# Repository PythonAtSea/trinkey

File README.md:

# Trinkey

Trinkey is a STM32 based keychain trinket. It has two Kailh switches, each with  a MBK low profile keycap and a reverse mounted SK6812MINI-E RGB LED. Additionally, there are two more reverse mounted SK6812MINI-E next to the keyring. It also has a male USB-A plug which powers the device and provides USB FS connectivity. 

## Screenshots

##### SVG export of schematic

##### Combined export of PCB

##### Top export of PCB

##### Bottom export of PCB

## Flashing Software

The Trinkey has pads for flashing using **S**erial **W**ire **D**ebug. If you're getting one of these thru [Hack Club Gadget Market](https://gadget.hackclub.com), it will be pre flashing with a bootloader that supports uploading code over USB using the Ardunio IDE. It will also have some sort of example program, but that is still TBD. I will also design a jig for holding contact against the test pads for flashing over SWD.

## Bill of Materials

| Item | Vendor | Price |
|------|--------|-------|
|PCB|JLCPCB|$70.43|
|[USB-A plug](https://www.digikey.com/en/products/detail/molex/0480370001/857603)|Digikey|$10.38|
|Shipping|Digikey|$4.99|
|Tariff|Digikey|$2.08|
|Sales tax|Digikey|$1.22|
|[SK6812MINI-E (25 pack)](https://keeb.io/products/sk-6812-mini-e-rgb-leds-12-pack)|Keebs.io|$5.99|
|[Kailh low profile switches](https://keeb.io/products/kailh-choc-low-profile-switches-v1)|Keebs.io|$7.20|
|[MBK PBT Blank keycaps](https://keeb.io/products/mbk-keycaps)|Keebs.io|$4.41|
|Shipping|Keebs.io|$7.90|
|[ST-LINK/V2 (mini)](https://www.waveshare.com/st-link-v2-mini-stm32.htm)|Waveshare|$8.99|
|Shipping|Waveshare|$10.00|
|**Total**| |**$133.59**|

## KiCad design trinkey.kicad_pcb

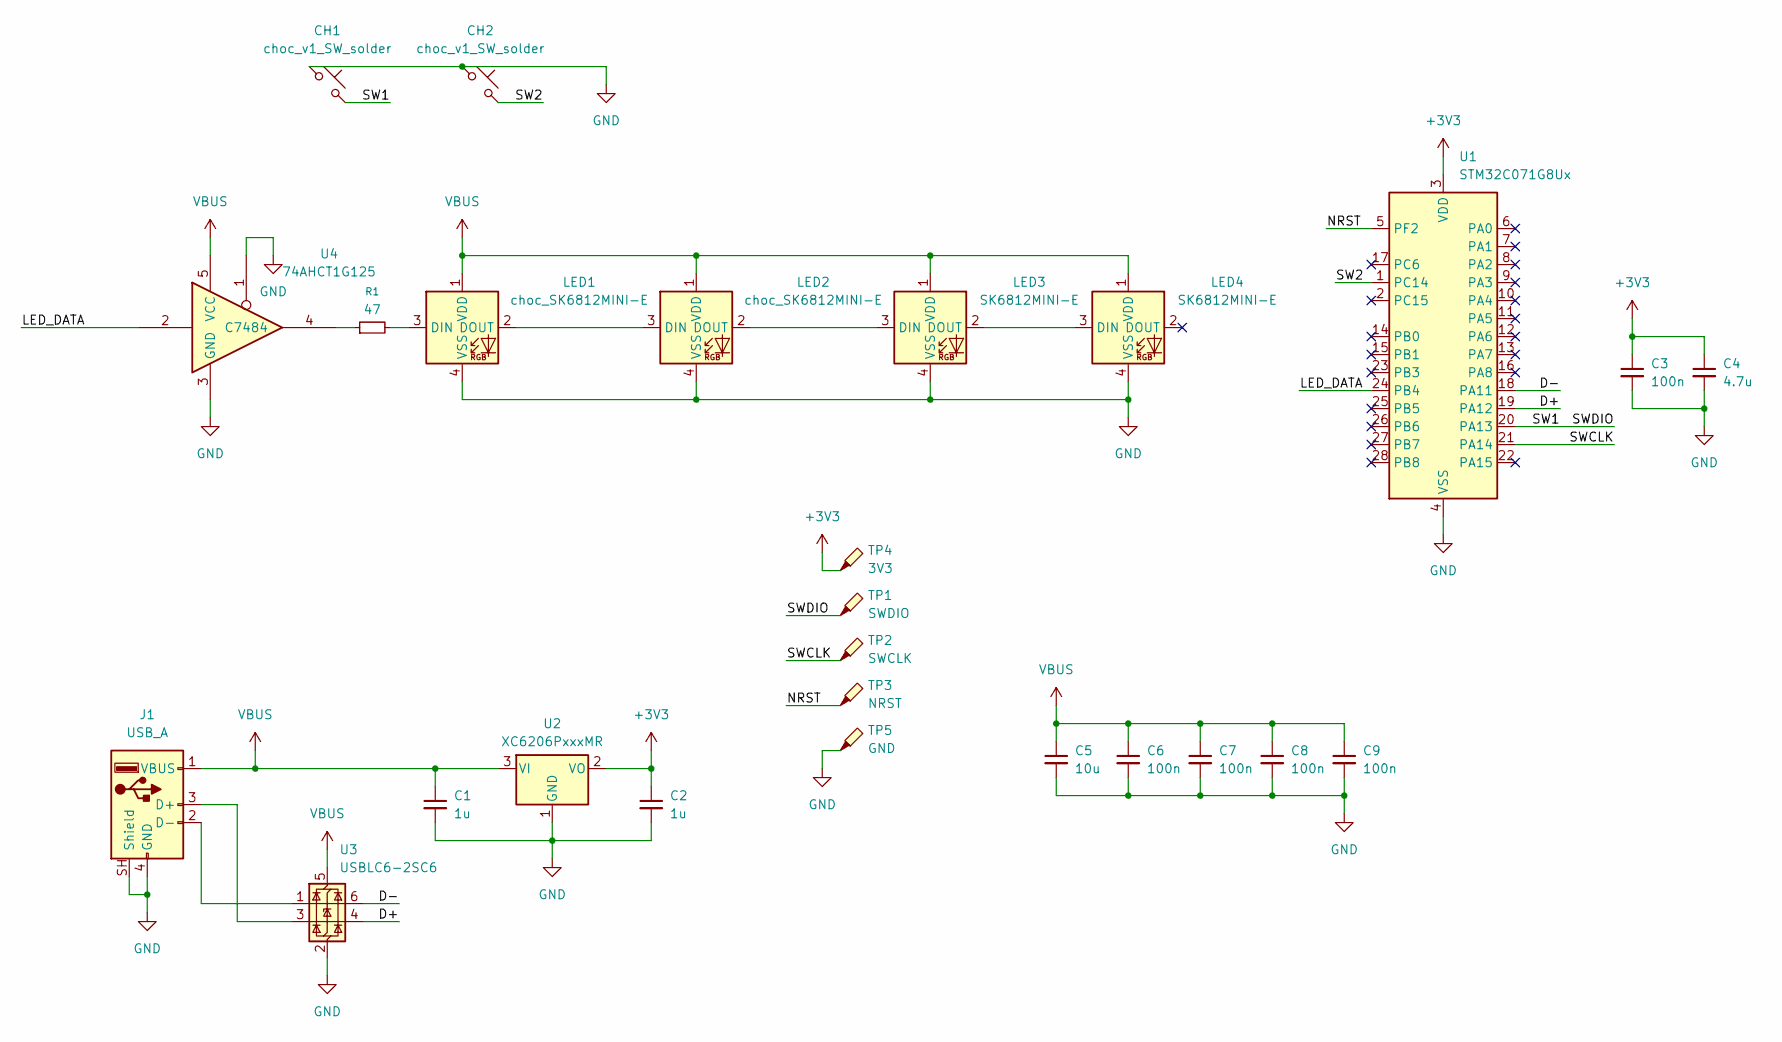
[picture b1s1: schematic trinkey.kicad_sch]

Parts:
C1, C2: 1u; C_0402_1005Metric; LCSC Part # C52923
C3, C6, C7, C8, C9: 100n; C_0402_1005Metric; LCSC Part # C1525
C4: 4.7u; C_0402_1005Metric; LCSC Part # C23733
C5: 10u; C_0402_1005Metric; LCSC Part # C15525
CH1, CH2: choc_v1_SW_solder; SW_choc_v1_1u
J1: USB_A; CONN_480370001_MOL
LED1, LED2: choc_SK6812MINI-E; LED_choc_6028R
LED3, LED4: SK6812MINI-E; LED_6028R
R1: 47; R_0402_1005Metric; LCSC Part # C25792
TP1: SWDIO; TestPoint_Pad_D1.0mm
TP2: SWCLK; TestPoint_Pad_D1.0mm
TP3: NRST; TestPoint_Pad_D1.0mm
TP4: 3V3; TestPoint_Pad_D1.0mm
TP5: GND; TestPoint_Pad_D1.0mm
U1: STM32C071G8Ux; QFN-28_4x4mm_P0.5mm; LCSC Part # C44521811
U2: XC6206PxxxMR; SOT-23-3; LCSC Part # C347376
U3: USBLC6-2SC6; SOT-23-6; LCSC Part # C2687116
U4: 74AHCT1G125; SOT-23-5; LCSC Part # C7484

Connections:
+3V3: C2.1, C3.1, C4.1, TP4.1 (1_1), U1.3 (VDD), U2.2 (VO)
/D+: U1.19 (PA12), U3.4 (I/O2)
/D-: U1.18 (PA11), U3.6 (I/O1)
/LED_DATA: U1.24 (PB4), U4.2
/NRST: TP3.1 (1_1), U1.5 (PF2)
/SW1: CH1.2, TP1.1 (1_1), U1.20 (PA13)
/SW2: CH2.2, U1.1 (PC14)
/SWCLK: TP2.1 (1_1), U1.21 (PA14)
GND: C1.2, C2.2, C3.2, C4.2, C5.2, C6.2, C7.2, C8.2, C9.2, CH1.1, CH2.1, J1.4 (GND), J1.SH (Shield), LED1.4 (VSS), LED2.4 (VSS), LED3.4 (VSS), LED4.4 (VSS), TP5.1 (1_1), U1.4 (VSS), U2.1 (GND), U3.2 (GND), U4.1, U4.3 (GND)
unnamed: J1.3 (D+), U3.3 (I/O2)
unnamed: J1.2 (D-), U3.1 (I/O1)
unnamed: LED1.3 (DIN), R1.2
unnamed: LED1.2 (DOUT), LED2.3 (DIN)
unnamed: LED2.2 (DOUT), LED3.3 (DIN)
unnamed: LED3.2 (DOUT), LED4.3 (DIN)
unnamed: R1.1, U4.4
VBUS: C1.1, C5.1, C6.1, C7.1, C8.1, C9.1, J1.1 (VBUS), LED1.1 (VDD), LED2.1 (VDD), LED3.1 (VDD), LED4.1 (VDD), U2.3 (VI), U3.5 (VBUS), U4.5 (VCC)

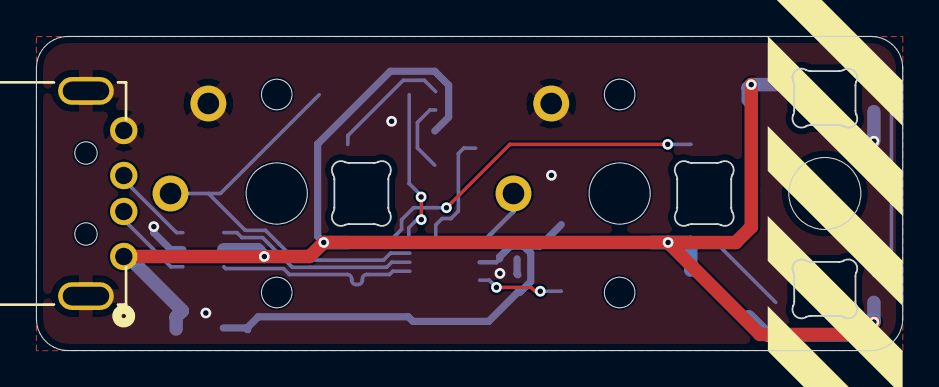
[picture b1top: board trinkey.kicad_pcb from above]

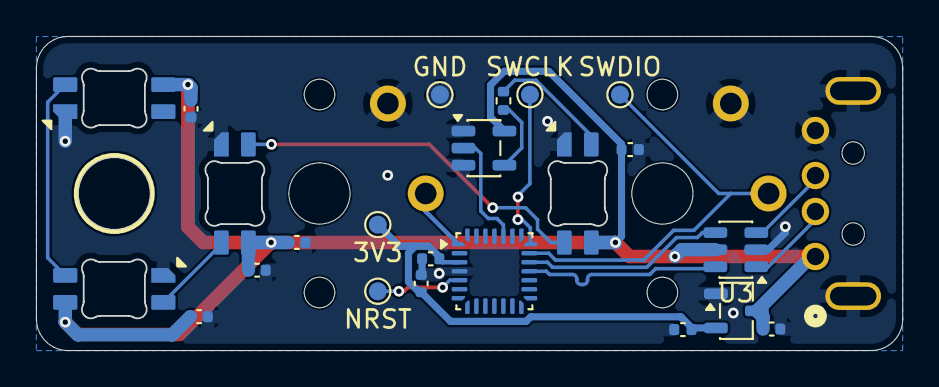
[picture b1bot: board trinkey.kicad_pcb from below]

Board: 2 copper layers, 48.1 x 17.5 mm, 26 parts (23 on the bottom side), 17 nets.

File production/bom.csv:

Designator,Footprint,Quantity,Value,LCSC Part #
"C1, C2",0402,2,1u,
"C3, C6, C7, C8, C9",0402,5,100n,
C4,0402,1,4.7u,
C5,0402,1,10u,
"CH1, CH2",SW_choc_v1_1u,2,choc_v1_SW_solder,
J1,CONN_480370001_MOL,1,USB_A,
"LED1, LED2",LED_choc_6028R,2,choc_SK6812MINI-E,
"LED3, LED4",LED_6028R,2,SK6812MINI-E,
R1,0402,1,47,
TP1,TestPoint_Pad_D1.0mm,1,SWDIO,
TP2,TestPoint_Pad_D1.0mm,1,SWCLK,
TP3,TestPoint_Pad_D1.0mm,1,NRST,
TP4,TestPoint_Pad_D1.0mm,1,3V3,
TP5,TestPoint_Pad_D1.0mm,1,GND,
U1,QFN-28_4x4mm_P0.5mm,1,STM32C071G8Ux,C44521811
U2,SOT-23-3,1,XC6206PxxxMR,C347376
U3,SOT-23-6,1,USBLC6-2SC6,C2687116
U4,SOT-23-5,1,74AHCT1G125,C7484
